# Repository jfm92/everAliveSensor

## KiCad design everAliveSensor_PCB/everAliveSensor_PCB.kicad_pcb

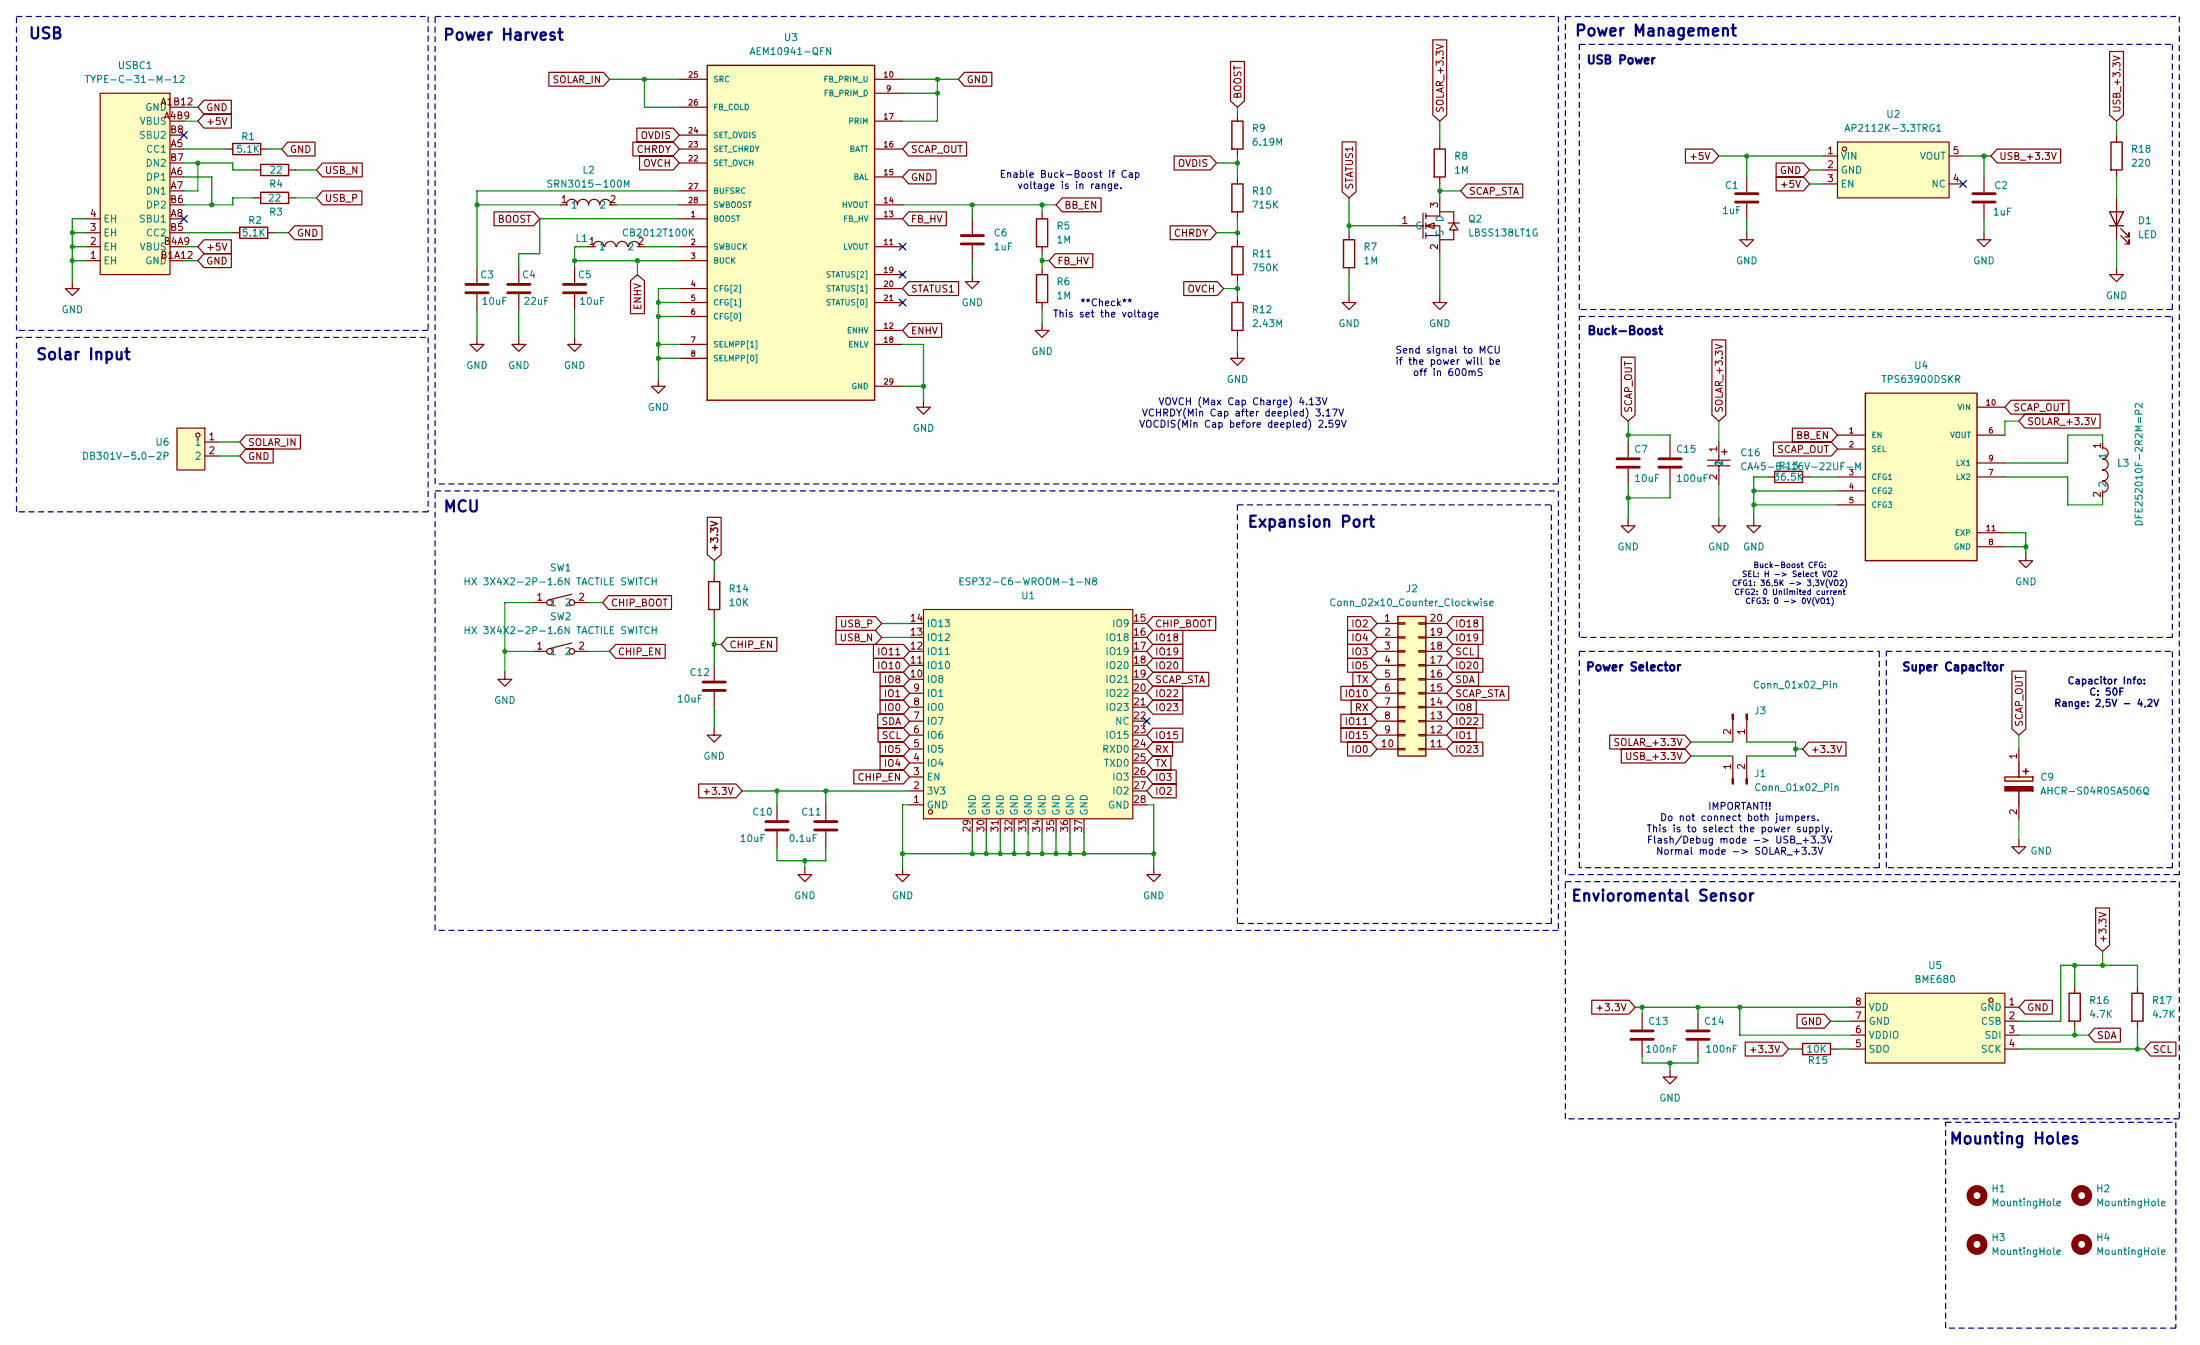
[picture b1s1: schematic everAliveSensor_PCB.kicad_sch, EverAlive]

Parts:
C1, C2, C6: 1uF; C_0805_2012Metric_Pad1.18x1.45mm_HandSolder
C3, C5, C7, C10, C12: 10uF; C_0805_2012Metric_Pad1.18x1.45mm_HandSolder
C4: 22uF; C_0805_2012Metric_Pad1.18x1.45mm_HandSolder
C9: AHCR-S04R0SA506Q; CAPPRD350W65D800H2700; Mouser Part Number 815-AHCR-S04R0SA506Q
C11: 0.1uF; C_0805_2012Metric_Pad1.18x1.45mm_HandSolder
C13, C14: 100nF; C_0805_2012Metric_Pad1.18x1.45mm_HandSolder
C15: 100uF; C_0603_1608Metric_Pad1.08x0.95mm_HandSolder
C16: CA45-B-16V-22UF-M; CAP-SMD_L3.5-W2.8-R-RD; MPN CA45-B-16V-22uF-M; LCSC Part C140371
D1: LED; LED_0805_2012Metric_Pad1.15x1.40mm_HandSolder
H1, H2, H3, H4: MountingHole; MountingHole_2.7mm_M2.5_Pad
J1, J3: Conn_01x02_Pin; PinHeader_1x02_P2.54mm_Vertical
J2: Conn_02x10_Counter_Clockwise; PinHeader_2x10_P2.54mm_Vertical
L1: CB2012T100K; L0805; MPN CB2012T100K; LCSC Part C223169
L2: SRN3015-100M; IND-SMD_L3.0-W3.0; MPN SRN3015-100M; LCSC Part C780208
L3: DFE252010F-2R2M=P2; L1008; MPN DFE252010F-2R2M=P2; LCSC Part C488330
Q2: LBSS138LT1G; SOT-23_L2.9-W1.3-P1.90-LS2.4-BR; MPN LBSS138LT1G; LCSC Part C8490
R1, R2: 5.1K; R_0805_2012Metric_Pad1.20x1.40mm_HandSolder
R3, R4: 22; R_0805_2012Metric_Pad1.20x1.40mm_HandSolder
R5, R6, R7, R8: 1M; R_0805_2012Metric_Pad1.20x1.40mm_HandSolder
R9: 6.19M; R_0805_2012Metric_Pad1.20x1.40mm_HandSolder
R10: 715K; R_0805_2012Metric_Pad1.20x1.40mm_HandSolder
R11: 750K; R_0805_2012Metric_Pad1.20x1.40mm_HandSolder
R12: 2.43M; R_0805_2012Metric_Pad1.20x1.40mm_HandSolder
R13: 36.5K; R_0805_2012Metric_Pad1.20x1.40mm_HandSolder
R14, R15: 10K; R_0805_2012Metric_Pad1.20x1.40mm_HandSolder
R16, R17: 4.7K; R_0805_2012Metric_Pad1.20x1.40mm_HandSolder
R18: 220; R_0805_2012Metric_Pad1.20x1.40mm_HandSolder
SW1, SW2: HX 3X4X2-2P-1.6N TACTILE SWITCH; KEY-SMD_L4.0-W3.0-LS4.9-1; MPN HX 3x4x2-2P-1.6N TACTILE SWITCH; LCSC Part C49234124
U1: ESP32-C6-WROOM-1-N8; WIRELM-SMD_ESP32-C6-WROOM-1; MPN ESP32-C6-WROOM-1-N8; LCSC Part C5366877
U2: AP2112K-3.3TRG1; SOT-25-5_L2.9-W1.6-P0.95-LS2.8-BL; MPN AP2112K-3.3TRG1; LCSC Part C51118
U3: AEM10941-QFN; QFN50P500X500X90-29N; PARTREV 1.4
U4: TPS63900DSKR; IC_TPS63900DSKR; PARTREV D
U5: BME680; LGA-8_L3.0-W3.0-P0.80-TR; MPN BME680; LCSC Part C125972
U6: DB301V-5.0-2P; CONN-TH_2P-P5.00_L7.6-W10.0; MPN DB301V-5.0-2P-BU-S; LCSC Part C395882
USBC1: TYPE-C-31-M-12; USB-C_SMD-TYPE-C-31-M-12_1; MPN TYPE-C-31-M-12; LCSC Part C165948

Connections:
+3.3V: C10.1, C11.1, C13.1, C14.1, J1.2, J3.1, R14.1, R15.1, R16.1, R17.1, U1.2 (3V3), U5.2 (CSB), U5.6 (VDDIO), U5.8 (VDD)
+5V: C1.1, U2.1 (VIN), U2.3 (EN), USBC1.A4B9 (VBUS), USBC1.B4A9 (VBUS)
BB_EN: C6.1, R5.1, U3.14 (HVOUT), U4.1 (EN)
BOOST: C4.1, R9.1, U3.1 (BOOST)
CHIP_BOOT: SW1.2, U1.15 (IO9)
CHIP_EN: C12.1, R14.2, SW2.2, U1.3 (EN)
CHRDY: R10.2, R11.1, U3.23 (SET_CHRDY)
ENHV: C5.1, L1.1, U3.3 (BUCK), U3.12 (ENHV)
FB_HV: R5.2, R6.1, U3.13 (FB_HV)
GND: C1.2, C2.2, C3.2, C4.2, C5.2, C6.2, C7.2, C9.2 (-), C10.2, C11.2, C12.2, C13.2, C14.2, C15.2, C16.2, D1.1 (K), Q2.2 (S), R1.2, R2.2, R6.2, R7.2, R12.2, R13.1, SW1.1, SW2.1, U1.1 (GND), U1.28 (GND), U1.29 (GND), U1.30 (GND), U1.31 (GND), U1.32 (GND), U1.33 (GND), U1.34 (GND), U1.35 (GND), U1.36 (GND), U1.37 (GND), U2.2 (GND), U3.4 (CFG[2]), U3.5 (CFG[1]), U3.6 (CFG[0]), U3.7 (SELMPP[1]), U3.8 (SELMPP[0]), U3.9 (FB_PRIM_D), U3.10 (FB_PRIM_U), U3.15 (BAL), U3.17 (PRIM), U3.18 (ENLV), U3.29 (GND), U4.4 (CFG2), U4.5 (CFG3), U4.8 (GND), U4.11 (EXP), U5.1 (GND), U5.7 (GND), U6.2, USBC1.1 (EH), USBC1.2 (EH), USBC1.3 (EH), USBC1.4 (EH), USBC1.A1B12 (GND), USBC1.B1A12 (GND)
IO0: J2.10, U1.8 (IO0)
IO1: J2.12, U1.9 (IO1)
IO2: J2.1, U1.27 (IO2)
IO3: J2.3, U1.26 (IO3)
IO4: J2.2, U1.4 (IO4)
IO5: J2.4, U1.5 (IO5)
IO8: J2.14, U1.10 (IO8)
IO10: J2.6, U1.11 (IO10)
IO11: J2.8, U1.12 (IO11)
IO15: J2.9, U1.23 (IO15)
IO18: J2.20, U1.16 (IO18)
IO19: J2.19, U1.17 (IO19)
IO20: J2.17, U1.18 (IO20)
IO22: J2.13, U1.20 (IO22)
IO23: J2.11, U1.21 (IO23)
unnamed: D1.2 (A), R18.2
unnamed: C3.1, L2.1, U3.27 (BUFSRC)
unnamed: L2.2, U3.28 (SWBOOST)
unnamed: L1.2, U3.2 (SWBUCK)
unnamed: R13.2, U4.3 (CFG1)
unnamed: L3.1, U4.9 (LX1)
unnamed: L3.2, U4.7 (LX2)
unnamed: R15.2, U5.5 (SDO)
unnamed: R1.1, USBC1.A5 (CC1)
unnamed: R2.1, USBC1.B5 (CC2)
unnamed: R4.1, USBC1.A7 (DN1), USBC1.B7 (DN2)
unnamed: R3.1, USBC1.A6 (DP1), USBC1.B6 (DP2)
OVCH: R11.2, R12.1, U3.22 (SET_OVCH)
OVDIS: R9.2, R10.1, U3.24 (SET_OVDIS)
RX: J2.7, U1.24 (RXD0)
SCAP_OUT: C7.1, C9.1 (+), C15.1, U3.16 (BATT), U4.2 (SEL), U4.10 (VIN)
SCAP_STA: J2.15, Q2.3 (D), R8.2, U1.19 (IO21)
SCL: J2.18, R17.2, U1.6 (IO6), U5.4 (SCK)
SDA: J2.16, R16.2, U1.7 (IO7), U5.3 (SDI)
SOLAR_+3.3V: C16.1, J3.2, R8.1, U4.6 (VOUT)
SOLAR_IN: U3.25 (SRC), U3.26 (FB_COLD), U6.1
STATUS1: Q2.1 (G), R7.1, U3.20 (STATUS[1])
TX: J2.5, U1.25 (TXD0)
USB_+3.3V: C2.1, J1.1, R18.1, U2.5 (VOUT)
USB_N: R4.2, U1.13 (IO12)
USB_P: R3.2, U1.14 (IO13)

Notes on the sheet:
Capacitor Info: C: 50F Range: 2,5V - 4,2V
Mounting Holes
Super Capacitor
Enable Buck-Boost if Cap voltage is in range.
Send signal to MCU if the power will be off in 600mS
VOVCH (Max Cap Charge) 4.13V VCHRDY(Min Cap after deepled) 3.17V VOCDIS(Min Cap before deepled) 2.59V
Solar Input
Power Selector
Power Management
Buck-Boost
Power Harvest
Expansion Port
Envioromental Sensor
IMPORTANT!! Do not connect both jumpers. This is to select the power supply. Flash/Debug mode -> USB_+3.3V Normal mode -> SOLAR_+3.3V
**Check** This set the voltage
Buck-Boost CFG: SEL: H -> Select VO2 CFG1: 36,5K -> 3,3V(VO2) CFG2: 0 Unlimited current CFG3: 0 -> 0V(VO1)
USB Power
USB
MCU

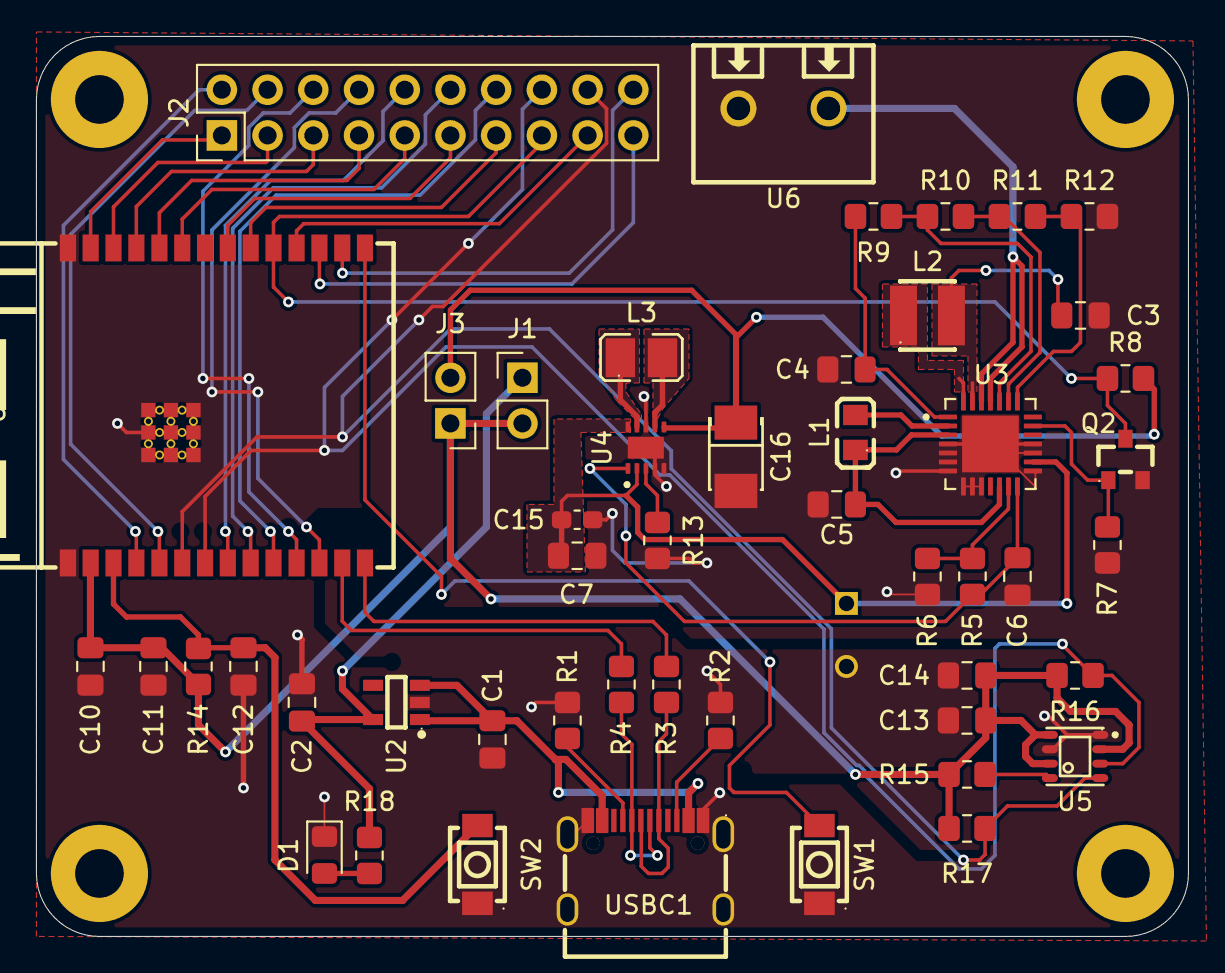
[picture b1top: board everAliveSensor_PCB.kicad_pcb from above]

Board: 2 copper layers, 64.0 x 50.0 mm, 54 parts (1 on the bottom side), 51 nets.

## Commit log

2026-05-23 Adding PCB design
2026-05-23 Adding project license
2026-05-23 Adding device enclosure
2026-05-23 Adding everAlive Firmware
2026-05-23 Updating .gitingore for the demo
2026-05-23 Adding demo example to interact with everAlive sensor
